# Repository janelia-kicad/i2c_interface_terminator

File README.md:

# i2c_interface_terminator

Authors:

    Peter Polidoro <polidorop@janelia.hhmi.org>

License:

    BSD

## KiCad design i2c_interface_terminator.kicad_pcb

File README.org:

#+TITLE: i2c_interface_terminator
#+AUTHOR: Peter Polidoro
#+EMAIL: peter@polidoro.io

* Repository Information
  - Author :: Peter Polidoro
  - License :: Open-Source Hardware

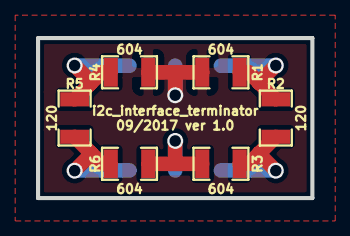
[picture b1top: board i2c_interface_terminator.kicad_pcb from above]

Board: 2 copper layers, 15.2 x 8.9 mm, 7 parts (1 on the bottom side), 6 nets.

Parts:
P1: HEADER_02X03_FEMALE_SMD; HEADER_02x03_FEMALE_SMD
R1, R3, R4, R6: 604; SM0805
R2, R5: 120; SM0805

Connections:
/DSCLM: P1.2, R2.2, R3.1
/DSCLP: P1.1, R1.2, R2.1
/DSDAM: P1.6, R5.2, R6.1
/DSDAP: P1.5, R4.2, R5.1
GND: P1.4, R3.2, R6.2
VAA: P1.3, R1.1, R4.1

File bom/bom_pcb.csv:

Item,Reference(s),Value,Quantity,Description,PartNumber,Vendor
1,P1,HEADER_02X03_FEMALE_SMD,1,CONN FEMALE 6POS DL .1IN GOLD SMD,S5712-ND,digikey
2,R1 R3 R4 R6,604_0805,4,RES SMD 604 OHM 1% 1/8W 0805,311-604CRCT-ND,digikey
3,R2 R5,120_0805,2,RES SMD 120 OHM 1% 1/8W 0805,311-120CRCT-ND,digikey

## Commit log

2017-09-14 Initial commit.
2017-09-14 Added template files.
2017-09-14 Added footprints and components.
2017-09-19 Rotated components.
2017-09-19 terminator_2_pair -> i2c_interface_terminator.
2017-09-19 Moved parts.
2017-09-21 Finished version 1.0.
2017-09-22 Removed extra libraries.
2018-01-08 Updated to v4.
2018-01-08 Added v4 files.
2018-01-08 Updated gitignore.
2018-03-09 Update license from software to hardware.
2018-04-12 README.md -> README.org.
2018-04-19 Added .DS_Store to .gitignore.
2018-05-16 Added generate_kicad_documentation submodule.
2018-05-17 Updated submodules.
2018-08-12 Removed v4 files.
2021-09-16 Update email address
2021-09-21 Remove ignored files
2022-02-22 Add guix files
2022-02-23 Add guix documentation
2024-05-31 Add board image
